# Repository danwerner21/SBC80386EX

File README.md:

# SBC-386EX

A single board computer built around the Intel 80386EX, an embedded 386
with most of a PC's support chips on the die. It plugs into a RetroBrew
ECB backplane or runs on its own, and with the BIOS in this repository
it boots **MS-DOS 6.22** and **COHERENT 4.2**, Mark Williams Company's
UNIX-like operating system.

**The board was designed by John Coffman** for
[RetroBrew Computers](https://www.retrobrewcomputers.org/). Its project
page, with the boards, the history and the community around it, is the
[SBC-386EX wiki page](https://www.retrobrewcomputers.org/doku.php?id=boards:sbc:sbc-386ex).
This repository holds the board's design files, its BIOS, and the
software that runs on it.

---

## The board

Version 2.0, from John Coffman's guide to the schematic
(`Hardware/SBC386ex2-schematic-guide.pdf`):

| | |
|---|---|
| CPU | Intel 80386EX, up to 33 MHz (a 66 MHz double-frequency oscillator for the fastest parts); on the board, or on an adapter board, the two footprints overlaid |
| FPU | 80387SX socket, run at the CPU's clock |
| Memory | one 72-pin SIMM, 4 to 64 MB, FPM or EDO, through a DRAM controller in two GAL16V8s; provision for a 32 KB static RAM |
| ROM | 64 KB EPROM, or 128, 256 or 512 KB flash, chosen by jumper |
| Serial | the 386EX's SIO0 at 3F8h, RS-232 on a 9-pin connector, from a 1.8432 MHz clock |
| Disk | an IDE connector laid out for a CompactFlash adapter, 8-bit programmed I/O |
| Clock | DS1302 real-time clock with battery-backed NVRAM |
| SD card | a microSD socket on the 386EX's synchronous serial unit (described on the schematic as "entirely experimental"; it works: see below) |
| Bus | 96-pin ECB connector, for RetroBrew cards: the Disk I/O V3 floppy controller, the VGA3 video and PS/2 keyboard board, and others |
| Front panel | four LEDs on port 1, a run/halt LED, reset |

The KiCad project, the schematic and board PDFs, a bill of materials and
the PLD equations are in [`Hardware/`](Hardware/).

---

## The BIOS

[`SBC386/bios`](SBC386/bios) is the board's ROM BIOS: John Coffman's,
from 2018, which brought the board up and laid the foundations, taken by
Dan Werner in 2026 to the point where it boots DOS. It gives the board a
PC-compatible BIOS interface on hardware that is not a PC:

- **POST** with a memory test and sizing, the ROM checked by CRC16 and
  then shadowed into DRAM, and the CPU clock measured
- **SETUP**, by pressing a key during POST, with its settings kept in the
  DS1302's NVRAM: disk geometry, floppy drives, the serial console, date
  and time, the boot device
- **Disks**: CompactFlash and IDE through INT 13h, CHS and the LBA
  extensions; floppy drives on the ECB Disk I/O V3, which has no DMA and
  is driven polled
- **Console**: the serial port, with VT100 translation, and the ECB VGA3
  colour display with a PS/2 keyboard, both at once
- **Clock**: INT 1Ah on the DS1302
- **A debug monitor**, SETUP entry 5, which every piece of hardware on the
  board was brought up with (commands in upper case, numbers in hex)

Notes for using it are in [`SBC386/bios/0README.TXT`](SBC386/bios/0README.TXT).
Two worth knowing first: **three Ctrl-^ in a row on the serial console
restart the board** (it has no Ctrl-Alt-Del), and **HIMEM.SYS needs
`/MACHINE:PS2`**, since there is no 8042 for it to drive A20 through.

How the BIOS went from never having run INT 13h to a DOS prompt, and why
things are as they are, is told in [`0BRINGUP.md`](0BRINGUP.md); what is
left is [`0TODO.md`](0TODO.md).

### Building the BIOS

The build runs on Linux. It needs:

| | |
|---|---|
| GNU make | |
| NASM | 2.08 is the version used; 2.09 is reported to have problems |
| Open Watcom C 1.9 | its tools on the `PATH`, and `WATCOM` set to where it is installed |
| gcc | for the build's helper programs |

1. **The helper programs** (`exe2rom`, `hex2bin`, `bin2hex`, `copt`) are
   in `SBC386/tools`, with their sources. Build them if the ones there do
   not run on your system:

   ```sh
   cd SBC386/tools
   make
   ```

2. **The ROM:**

   ```sh
   cd SBC386/bios
   make
   ```

   This builds `rom064.hex`, the 64 KB image for an EPROM, and
   `rom128.hex`, `rom256.hex` and `rom512.hex`, the same BIOS placed at
   the top of a 128, 256 or 512 KB flash part. They are Intel HEX, for
   any device programmer. `make MONITOR=0` leaves the debug monitor out,
   which frees about 25 KB of the 64 KB.

3. **Program** the part that matches the ROM jumper, fit it, and connect
   a terminal to the serial port at **9600 baud, 8 data bits, no
   parity**. POST runs there; press a key during it for SETUP.

---

## The SD card under DOS

[`SBC386/sdcard`](SBC386/sdcard) has a DOS driver for the on-board
microSD socket, and the program it was brought up with:

- **`SD.SYS`**: `DEVICE=SD.SYS` in `CONFIG.SYS` gives the card's first
  FAT12 or FAT16 partition a drive letter (DOS 4 or later)
- **`SDTEST.COM`**: the bring-up program, which tests the socket a step
  at a time, from the pins to timed reads and a write test on a sector
  outside the partition

Both build with `make` in that directory (GNU make and NASM). How the
socket was made to work, given a serial unit that only moves 16-bit
words and a clock line that floats between transfers, is set down in the
comments of `sdtest.asm`.

---

## COHERENT

[`Coherent/`](Coherent/) is a port of **COHERENT 4.2** to the board. It
comes up multi-user, with a login on the serial port and another on the
VGA3 screen and keyboard when one is fitted. Its drivers cover the
board's IDE port and CompactFlash, the ECB floppy controller (read,
write and format), the VGA3 console, and the microSD socket, so files
move to and from DOS on SD cards and diskettes.

It is installed on the board from five diskettes, the original 4.2.10
kit with a boot diskette and a supplement made for the board. **The
diskette images, the installation directions and everything about
building it are in [`Coherent/README.md`](Coherent/README.md).**

---

## What is where

| Path | |
|---|---|
| [`Hardware/`](Hardware/) | the board: KiCad project, schematic and PCB PDFs, the schematic guide, bill of materials, PLD equations |
| [`SBC386/bios/`](SBC386/bios/) | the BIOS |
| [`SBC386/tools/`](SBC386/tools/) | the BIOS build's helper programs and their sources |
| [`SBC386/sdcard/`](SBC386/sdcard/) | `SD.SYS` and `SDTEST.COM`, for the microSD socket under DOS |
| [`SBC386/ATBIOS/`](SBC386/ATBIOS/) | an IBM AT BIOS listing, the reference for what DOS expects |
| [`Coherent/`](Coherent/) | the COHERENT port: install diskettes, kernel source and changes, tools |
| [`TestROMS/`](TestROMS/), [`EX2-11/`](EX2-11/), [`386v2/`](386v2/) | John Coffman's test ROMs, early BIOS work and PLD files from the board's bring-up in 2018 |
| [`0BRINGUP.md`](0BRINGUP.md), [`0TODO.md`](0TODO.md) | the BIOS bring-up record, and what is left |

---

## Credits

- **John Coffman** designed the SBC-386EX, wrote its first BIOS and the
  tools it is built with, and brought the board up in 2018. See the
  [RetroBrew Computers wiki](https://www.retrobrewcomputers.org/doku.php?id=boards:sbc:sbc-386ex).
- **Dan Werner** took the BIOS to MS-DOS in 2026, and ported COHERENT
  with the board's drivers, including the SD cards.
- **Mark Williams Company** wrote COHERENT, released as open source in
  2015.
- The [RetroBrew Computers](https://www.retrobrewcomputers.org/) community,
  whose ECB bus and boards this one shares.

## Licence

The BIOS is free software under the GNU General Public License, version
3 or later: see [`SBC386/bios/COPYING`](SBC386/bios/COPYING). COHERENT's
own licence, and that of the work on it here, are described in
[`Coherent/README.md`](Coherent/README.md).

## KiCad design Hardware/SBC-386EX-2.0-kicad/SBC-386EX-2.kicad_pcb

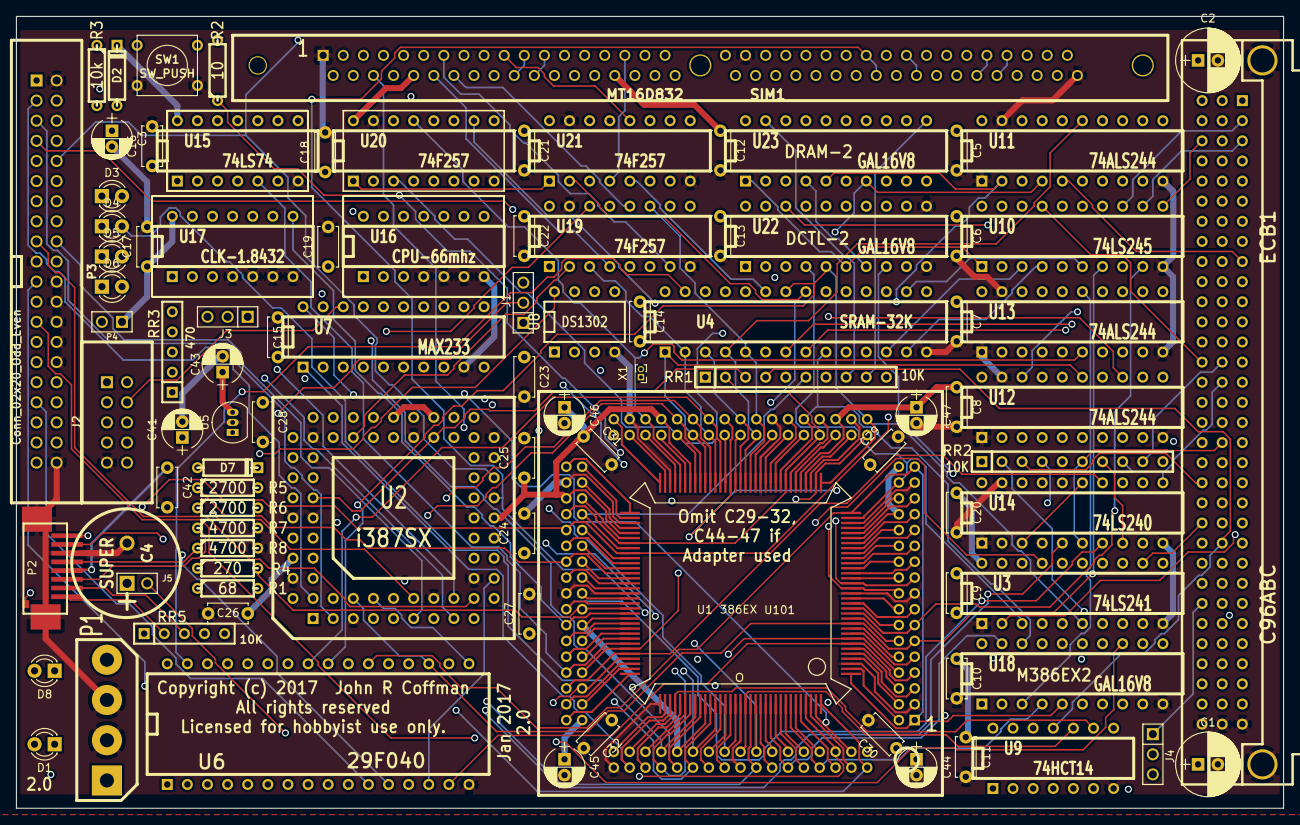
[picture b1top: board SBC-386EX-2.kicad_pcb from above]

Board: 4 copper layers, 160.0 x 100.0 mm, 96 parts (0 on the bottom side), 215 nets.

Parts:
C1, C2: 22uF; CP_Radial_D8.0mm_P2.50mm
C3: 10uf; CP_Radial_D5.0mm_P2.00mm
C4: SUPER; SuperCap5
C5, C6, C7, C8, C9, C10, C11, C12, C13, C14, C15, C16, C17, C18, C19, C20, C21, C22, C23, C24, C25, C26, C27, C28, C29, C30, C31, C32: C; C_Disc_D5.0mm_W2.5mm_P5.00mm
C41: 4.7uF; CP_Radial_D5.0mm_P2.00mm
C42: 0.1; C_Disc_D5.0mm_W2.5mm_P5.00mm
C43, C44, C45, C46, C47: 10uF; CP_Radial_D5.0mm_P2.00mm
D1: R/G LED; LED_D3.0mm
D2: DIODE; D3
D3, D4, D5, D6: LED; LED_D3.0mm
D7: 1N4148; D3
D8: SD LED; LED_D3.0mm
ECB1: C96ABC; C96ABCM-RA
J1, J3, J4: Conn_01x03; PIN_ARRAY_3X1
J2: Conn_02x05_Odd_Even; SHROUDED_5x2
J5: Conn_01x02; PIN_ARRAY_2X1
P1: Conn_01x04; PCpower4
P2: microSD-01; microSD-Molex-47309
P3: Conn_02x20_Odd_Even; SHROUDED_20X2
P4: CONN_2; PIN_ARRAY_2X1
R1: 68; R3
R2: 10; R3
R3: 10k; R3
R4: 270; R3
R5, R6: 2700; R3
R7, R8: 4700; R3
RR1, RR2: 10K; r_pack9
RR3: 470; r_pack4
RR5: 10K; r_pack4
SIM1: MT16D832; DRAM-72-2021
SW1: SW_PUSH; SW_PUSH_SMALL
U1: I386EX_passive; i386EX-132-adapter
U2: i387SX; 80188
U3: 74LS241; DIP-20__300
U4: SRAM-32K; DIP-28__300
U5: LP2950-3.3_TO92; TO-92_Inline_Narrow_Oval
U6: 29F040; DIP-32__600
U7: MAX233; DIP-20__300
U8: DS1302; DIP-8__300
U9: 74HCT14; DIP-14__300
U10: 74LS245; DIP-20__300
U11, U12, U13: 74ALS244; DIP-20__300
U14: 74LS240; DIP-20__300
U15: 74LS74; DIP-14__300
U16: CPU-66mhz; DIP-14__300
U17: CLK-1.8432; DIP-14__300
U18, U22, U23: GAL16V8; DIP-20__300
U19, U20, U21: 74F257; DIP-16__300
U101: I386EX_PQFP; PQFP-132_i386_JRC
X1: CRYSTAL; Tuning_Fork_Header_Straight_1x02_Pitch1.00mm

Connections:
/DRAM/CAS: U22.12, U23.3
/DRAM/DR_A0: SIM1.12, U19.4
/DRAM/DR_A1: SIM1.13, U19.7
/DRAM/DR_A2: SIM1.14, U19.12
/DRAM/DR_A3: SIM1.15, U19.9
/DRAM/DR_A4: SIM1.16, U20.4
/DRAM/DR_A5: SIM1.17, U20.7
/DRAM/DR_A6: SIM1.18, U20.12
/DRAM/DR_A7: SIM1.28, U20.9
/DRAM/DR_A8: SIM1.31, U21.4
/DRAM/DR_A9: SIM1.32, U21.7
/DRAM/DR_A10: SIM1.19, U21.12
/DRAM/DR_A11: SIM1.29, U21.9
/DRAM/MUX: U19.1, U20.1, U21.1, U22.13
/DRAM/RAS: U22.14, U23.2
/DRAM/~CAS20: SIM1.40, SIM1.41, U23.13
/DRAM/~CAS31: SIM1.42, SIM1.43, U23.18
/DRAM/~RAS0: SIM1.44, U23.15
/DRAM/~RAS1: SIM1.45, U23.14
/DRAM/~RAS2: SIM1.34, U23.16
/DRAM/~RAS3: SIM1.33, U23.17
/DRAM/~WE: SIM1.47, U23.12
/SDcard/SD-CLK: P2.5, R6.2, R8.1
/SDcard/SD-DI: P2.3, R5.2, R7.1
/SDcard/VDD: C41.1, C42.1, D7.1, D8.1, P2.4, RR5.1, U5.1
/UART-SIO/R_RXD: J2.3, U7.4
/UART-SIO/R_TXD: J2.5, U7.5
/UART-SIO/~R_CTS: J2.6, J3.1
/UART-SIO/~R_DSR: J2.2, J3.3
/UART-SIO/~R_DTR: J2.4, J2.7, U7.18
/bus-IDE/IDE-PIN20: P3.20, P4.2
A1: P3.33, U1.42, U4.9, U6.11, U11.4, U18.18, U23.7, U101.42
A2: P3.36, U1.43, U2.48, U4.8, U6.10, U11.6, U18.7, U19.2, U101.43
A3: U1.44, U4.7, U6.9, U11.8, U18.8, U19.5, U101.44
A4: U1.45, U4.6, U6.8, U11.11, U19.14, U101.45
A5: U1.48, U4.5, U6.7, U11.13, U19.11, U101.48
A6: U1.49, U4.4, U6.6, U11.15, U20.2, U101.49
A7: U1.50, U4.3, U6.5, U11.17, U20.5, U101.50
A8: U1.51, U4.25, U6.27, U12.2, U20.14, U101.51
A9: U1.52, U4.24, U6.26, U12.4, U20.11, U101.52
A10: U1.53, U4.21, U6.23, U12.6, U21.2, U101.53
A11: U1.54, U4.23, U6.25, U12.8, U21.5, U101.54
A12: U1.55, U4.2, U6.4, U12.11, U19.3, U101.55
A13: U1.56, U4.26, U6.28, U12.13, U19.6, U101.56
A14: U1.57, U4.1, U6.29, U12.15, U19.13, U101.57
A15: U1.58, U6.3, U12.17, U19.10, U101.58
A16: U1.59, U6.2, U13.2, U20.3, U101.59
A17: J1.1, U1.61, U13.4, U20.6, U101.61
A18: U1.62, U6.1, U13.6, U20.13, U101.62
A19: U1.63, U13.8, U20.10, U101.63
A20: U1.65, U21.3, U101.65
A21: U1.66, U21.6, U101.66
A22: U1.67, U21.14, U23.8, U101.67
A23: U1.68, U2.45, U21.13, U101.68
A24: U1.70, U21.11, U23.9, U101.70
A25: U1.72, U21.10, U101.72
B_A0: ECB1.C5, U11.18
B_A1: ECB1.C7, U11.16
B_A2: ECB1.A6, U11.14
B_A3: ECB1.C6, U11.12
B_A4: ECB1.A7, U11.9
B_A5: ECB1.A8, U11.7
B_A6: ECB1.A9, U11.5
B_A7: ECB1.C9, U11.3
B_A8: ECB1.C8, U12.18
B_A9: ECB1.A30, U12.16
B_A10: ECB1.C18, U12.14
B_A11: ECB1.C17, U12.12
B_A12: ECB1.C27, U12.9
B_A13: ECB1.A29, U12.7
B_A14: ECB1.A18, U12.5
B_A15: ECB1.C28, U12.3
B_A16: ECB1.C10, U13.18
B_A17: ECB1.C12, U13.16
B_A18: ECB1.C13, U13.14
B_A19: ECB1.A14, U13.12
B_D0: ECB1.C2, U10.18
B_D1: ECB1.C14, U10.17
B_D2: ECB1.C4, U10.16
B_D3: ECB1.A4, U10.15
B_D4: ECB1.A5, U10.14
B_D5: ECB1.A2, U10.13
B_D6: ECB1.A3, U10.12
B_D7: ECB1.C3, U10.11
B_DT_~R: ECB1.B27, U13.7
B_HALT: D1.1, U14.5
B_VBAT: ECB1.A24, J5.2
B_~CLK: ECB1.C29, U13.3
B_~DREQ: ECB1.B23, RR1.4, U9.11
B_~HALT: ECB1.C25, R1.2, U14.3, U14.15
B_~INT: ECB1.B20, ECB1.C21, RR2.4, U14.2
B_~IORQ: ECB1.A27, U3.16
B_~IR2: ECB1.B19, RR2.5, U14.4
B_~IR3: ECB1.B18, RR2.6, U14.6
B_~IR5: ECB1.B16, RR2.7, U14.8
B_~IR6: ECB1.B15, RR2.8, U14.11
B_~IR7: ECB1.B14, RR2.9, U14.13
B_~M1: ECB1.A20, RR1.7, U13.9
B_~MREQ: ECB1.C30, U13.5
B_~NMI: ECB1.C20, RR2.3, U9.5
B_~RD: ECB1.C24, U3.14
B_~RESET: ECB1.C31, J4.2
B_~RESOUT: ECB1.C26, J4.1, U3.18
B_~WR: ECB1.C22, U3.12
CLK2: U1.115, U2.54, U16.8, U16.11, U22.1, U101.115
CLKOUT: U1.103, U9.9, U101.103
COMCLK: U1.87, U15.3, U17.8, U17.11, U101.87
CPU_PU: RR1.2, U1.41, U1.73, U1.99, U101.41, U101.73, U101.99
D0: P3.17, SIM1.2, SIM1.3, U1.5, U2.19, U4.11, U6.13, U10.2, U101.5
D1: P3.15, SIM1.4, SIM1.5, U1.6, U2.20, U4.12, U6.14, U10.3, U101.6
D2: P3.13, SIM1.6, SIM1.7, U1.7, U2.23, U4.13, U6.15, U10.4, U101.7
D3: P3.11, SIM1.8, SIM1.9, U1.8, U2.8, U4.15, U6.17, U10.5, U101.8
D4: P3.9, SIM1.20, SIM1.21, U1.10, U2.7, U4.16, U6.18, U10.6, U101.10
D5: P3.7, SIM1.22, SIM1.23, U1.11, U2.6, U4.17, U6.19, U10.7, U101.11
D6: P3.5, SIM1.24, SIM1.25, U1.12, U2.3, U4.18, U6.20, U10.8, U101.12
D7: P3.3, SIM1.26, SIM1.27, U1.13, U2.2, U4.19, U6.21, U10.9, U101.13
D8: P3.4, SIM1.49, SIM1.50, U1.14, U2.24, U101.14
D9: P3.6, SIM1.51, SIM1.52, U1.16, U2.28, U101.16
D10: P3.8, SIM1.53, SIM1.54, U1.18, U2.29, U101.18
D11: P3.10, SIM1.55, SIM1.56, U1.19, U2.30, U101.19
D12: P3.12, SIM1.57, SIM1.58, U1.20, U2.16, U101.20
D13: P3.14, SIM1.60, SIM1.61, U1.21, U2.15, U101.21
D14: P3.16, SIM1.62, SIM1.63, U1.22, U2.12, U101.22
D15: P3.18, SIM1.64, SIM1.65, U1.23, U2.11, U101.23
DREQ0: U1.117, U9.10, U101.117
DREQ1: P3.21, U1.118, U101.118
DSIZE: RR1.8, SIM1.67, U23.19
DT_~R: U1.30, U2.41, U10.1, U13.13, U22.6, U23.1, U101.30
D_~C: U1.29, U13.11, U22.8, U101.29
FPU_PU: RR1.3, U2.40, U2.59
GND: C1.2, C2.2, C3.2, C4.2, C5.2, C6.2, C7.2, C8.2, C9.2, C10.2, C11.2, C12.2, C13.2, C14.2, C15.2, C16.2, C17.2, C18.2, C19.2, C20.2, C21.2, C22.2, C23.2, C24.2, C25.2, C26.2, C27.2, C28.2, C29.2, C30.2, C31.2, C32.2, C41.2, C42.2, C43.2, C44.2, C45.2, C46.2, C47.2, ECB1.A32, ECB1.B32, ECB1.C32, ECB1.HOLE, J2.9, P1.2, P1.3, P2.6, P2.GND, P3.2, P3.19, P3.22, P3.24, P3.26, P3.28, P3.30, P3.40, R7.2, R8.2, SIM1.1, SIM1.39, SIM1.72, SW1.2, U1.3, U1.17, U1.31, U1.36, U1.46, U1.64, U1.69, U1.83, U1.97, U1.100, U1.116, U1.130, U1.134, U1.136, U2.5, U2.14, U2.21, U2.25, U2.27, U2.32, U2.34, U2.38, U2.42, U2.53, U2.55, U2.60, U2.61, U2.63, U2.66, U3.1, U3.10, U4.14, U5.2, U6.16, U7.6, U7.9, U8.4, U9.7, U10.10, U11.1, U11.10, U11.19, U12.1, U12.10, U12.19, U13.1, U13.10, U13.19, U14.1, U14.10, U14.19, U15.7, U16.4, U16.5, U16.6, U16.7, U17.4, U17.5, U17.6, U17.7, U18.10, U19.8, U19.15, U20.8, U20.15, U21.8, U21.15, U22.10, U22.11, U23.10, U101.3, U101.17, U101.31, U101.36, U101.46, U101.64, U101.69, U101.83, U101.97, U101.100, U101.116, U101.130
HALT: U14.17, U22.18
IDE-IR14: P3.31, U1.96, U101.96
IR1: U1.80, U14.18, U101.80
IR5: U1.82, U14.12, U101.82
IR6: U1.84, U14.9, U101.84
IR7: U1.85, U14.7, U101.85
IR9: U1.94, U14.16, U101.94
IR13: U1.95, U14.14, U101.95
M_~IO: U1.27, U2.44, U101.27
NMI: U1.90, U9.6, U101.90
unnamed: C4.1, J5.1, U8.8
unnamed: D1.2, R1.1
unnamed: D3.1, RR3.5
unnamed: D4.1, RR3.4
unnamed: D5.1, RR3.3
unnamed: D6.1, RR3.2
unnamed: D8.2, R4.1
unnamed: J1.2, U6.30
unnamed: J3.2, U7.19
unnamed: J4.3, R2.2, SW1.1
unnamed: P2.1, RR5.2
unnamed: P2.8, RR5.5
unnamed: U1.24, U101.24
unnamed: U1.25, U101.25
unnamed: U1.26, U101.26
unnamed: U1.76, U101.76
unnamed: U1.114, U101.114
unnamed: U1.120, U101.120
unnamed: U1.128, U101.128
unnamed: U7.10, U7.16
unnamed: U7.11, U7.15
unnamed: U7.12, U7.17
unnamed: U8.2, X1.1
unnamed: U8.3, X1.2
unnamed: U9.8, U13.17
unnamed: U15.2, U15.6
PEREQ: RR1.6, U1.74, U1.89, U2.56, U101.74, U101.89
RESET: U1.110, U2.51, U9.2, U9.3, U101.110
RTC_CLK: U1.104, U8.7, U101.104
RTC_DQ: RR1.5, U1.101, U8.6, U101.101
RTC_~RESET: U1.105, U8.5, U101.105
SD-CXS: R6.1, U1.77, U1.98, U101.77, U101.98
SD-RXS: P2.7, RR5.4, U1.78, U101.78
SD-TXS: R5.1, U1.79, U101.79
TMRCLK0: U1.93, U15.5, U101.93
T_RXD0: U1.129, U7.3, U101.129
T_TXD0: U1.131, U7.2, U101.131
VCC: C1.1, C2.1, C5.1, C6.1, C7.1, C8.1, C9.1, C10.1, C11.1, C12.1, C13.1, C14.1, C15.1, C16.1, C17.1, C18.1, C19.1, C20.1, C21.1, C22.1, C23.1, C24.1, C25.1, C26.1, C27.1, C28.1, C29.1, C30.1, C31.1, C32.1, C43.1, C44.1, C45.1, C46.1, C47.1, D2.2, D7.2, ECB1.A1, ECB1.B1, ECB1.C1, J1.3, P1.4, P4.1, R3.1, RR1.1, RR2.1, RR3.1, SIM1.10, SIM1.30, SIM1.59, U1.9, U1.15, U1.28, U1.38, U1.47, U1.60, U1.71, U1.81, U1.88, U1.109, U1.121, U1.127, U1.133, U1.135, U2.4, U2.9, U2.13, U2.22, U2.26, U2.31, U2.33, U2.37, U2.39, U2.43, U2.46, U2.50, U2.58, U2.62, U2.64, U3.20, U4.28, U5.3, U6.32, U7.7, U8.1, U9.14, U10.20, U11.20, U12.20, U13.20, U14.20, U15.1, U15.4, U15.14, U16.14, U17.14, U18.20, U19.16, U20.16, U21.16, U22.20, U23.20, U101.9, U101.15, U101.28, U101.38, U101.47, U101.60, U101.71, U101.81, U101.88, U101.109, U101.121, U101.127
~ADS: U1.40, U2.47, U22.2, U101.40
~BHE: U1.39, U23.6, U101.39
~BLE: P3.35, U1.37, U4.10, U6.12, U11.2, U23.5, U101.37
~BUSY: U1.92, U2.36, U101.92
~CS-IDE0: P3.37, U18.16
~CS-IDE1: P3.38, U18.17
~CS_DRAM: U1.124, U18.2, U101.124
~CS_LIO: U1.123, U18.1, U101.123
~CS_ROM: U1.1, U1.33, U6.22, U18.5, U101.1, U101.33
~CS_SRAM: U1.126, U4.20, U18.4, U101.126
~CS_XIO: U1.122, U3.4, U18.19, U101.122
~CS_XMEM: U1.125, U13.15, U18.3, U101.125
~DACK1: P3.29, U1.112, U18.6, U101.112
~DAT_EN: U10.19, U18.15
~DRAM: U18.14, U22.3
~EOP: ECB1.B26, RR2.2, U1.113, U101.113
~ERROR: U1.91, U2.35, U101.91
~IDE-RD: P3.25, U18.13
~IDE-WR: P3.23, U18.12
~LBA: U1.4, U3.19, U101.4
~LITE_0: D3.2, U1.106, U101.106
~LITE_1: D4.2, U1.107, U101.107
~LITE_2: D5.2, U1.108, U101.108
~LITE_3: D6.2, U1.111, U101.111
~RD: U1.34, U3.6, U4.22, U6.24, U18.11, U22.5, U101.34
~READY: U1.32, U2.49, U3.3, U22.4, U101.32
~READYO: U2.57, U3.17
~REFRESH: U1.2, U22.7, U23.4, U101.2
~RESET: P3.1, U3.2, U9.4
~RESET_0: C3.1, D2.1, R2.1, R3.2, U1.119, U9.1, U101.119
~SD-CD: P2.CD, RR1.10, U1.75, U101.75
~SD-CS: P2.2, R4.2, RR5.3, U1.86, U101.86
~SZ32: RR1.9, SIM1.68, U23.11
~T_CTS0: U1.132, U7.20, U101.132
~T_RTS0: U1.102, U7.1, U101.102
~WR: U1.35, U3.8, U4.27, U6.31, U18.9, U101.35

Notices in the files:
Hardware/SBC-386EX-2.0-kicad/SBC-386EX-2.kicad_pcb:
Copyright (c) 2017  John R Coffman
All rights reserved
